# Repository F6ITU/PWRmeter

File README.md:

This millwattmeter project has been driven by 

(c) Dietmar Krause, DL2SBA

License see https://creativecommons.org/licenses/by/4.0/

All software update, construction and calibration hints could be found at 

http://www.dl2sba.com/index.php/elektronik/messtechnik/rf-powermeter

This board  supports two power rails, an Arduino nano and 
3 Molex kk connectors to fit the power input, an Itead Nextion touche display, and
an "all in one" RF detector designed by SV1AFN including : 
An AD8318 det.log, a 12 bits ADC and a low noise 5V power supply. All details at 

https://www.sv1afn.com/ad8318.html

This is a one day project, even for unexperimented ham/hackers. 

Board's dimension is 5x10 cm. 
Two boards could be panelized to fit in a 10x10 standard pcb format
(Itead, Dirt Cheap pcb, Seeed Studio etc)

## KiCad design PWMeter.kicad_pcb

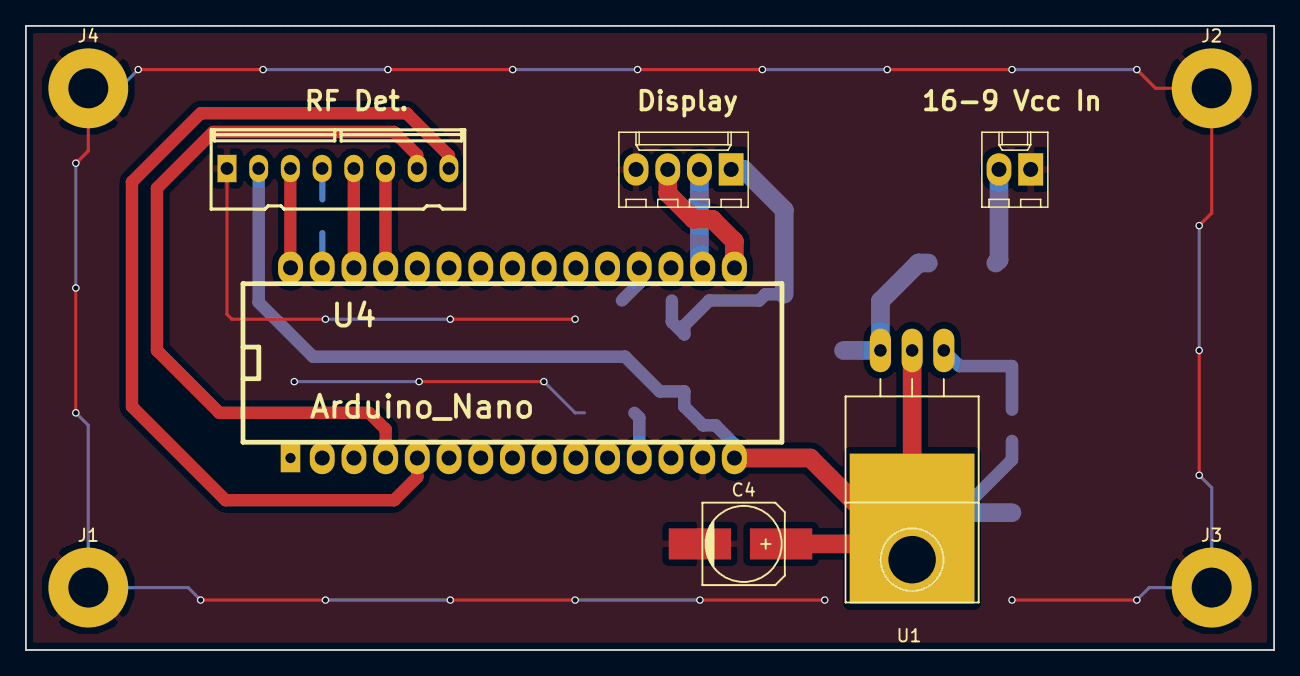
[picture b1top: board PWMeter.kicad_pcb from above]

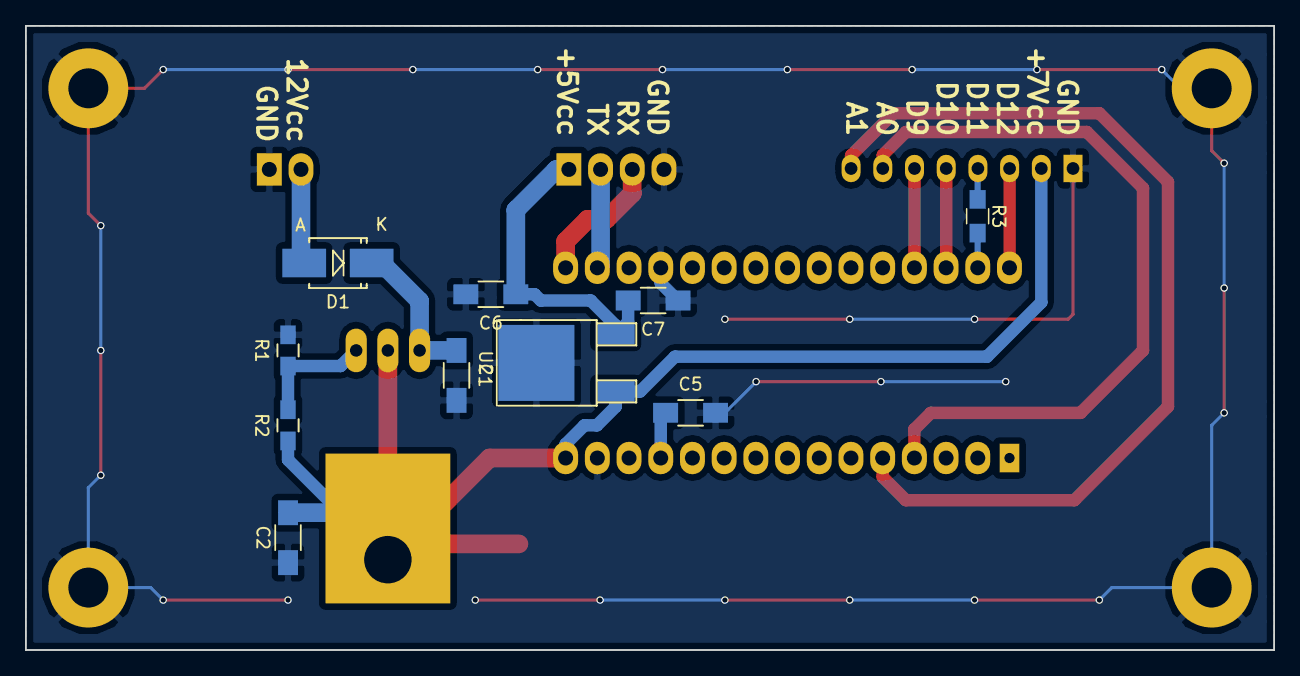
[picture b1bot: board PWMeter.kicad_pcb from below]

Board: 2 copper layers, 100.0 x 50.0 mm, 20 parts (10 on the bottom side), 16 nets.

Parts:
 : 16/9V in; Molex_KK-6410-02_02x2.54mm_Straight
 #2: Display; Molex_KK-6410-04_04x2.54mm_Straight
 #3: kk100_22-23-2081
C1, C2, C5, C6, C7: 100n; C_1206_HandSoldering
C4: 1500uF; c_elec_6.3x7.7
D1: D_Schottky; SMB_Handsoldering
J1, J2, J3, J4: TEST_1P; MountingHole_3.2mm_M3_Pad
R1: 110; C_0805_HandSoldering
R2: 240; C_0805_HandSoldering
R3: R; R_0805_HandSoldering
U1: LM317T; TO-220_Neutral123_Horizontal_LargePads
U2: MC78M05CDT; TO-252-2Lead
U4: Arduino_Nano; arduino_nano

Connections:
+5C: #2.1, C6.1, C7.2, U2.3
+8V: #3.2, C2.1, C4.1, R2.1, U1.2, U2.1, U4.15
+12V: .2, D1.2
GND: .1, #2.4, #3.1, C1.2, C2.2, C4.2, C5.2, C6.2, C7.1, J1.1, J2.1, J3.1, J4.1, R1.2, U2.2, U4.14, U4.19
unnamed: C1.1, D1.1, U1.3
unnamed: C5.1, U4.12
unnamed: #3.3, U4.30
unnamed: #3.4, R3.1
unnamed: #3.5, U4.28
unnamed: #3.6, U4.27
unnamed: #3.7, U4.4
unnamed: #3.8, U4.5
unnamed: #2.2, U4.17
unnamed: #2.3, U4.16
unnamed: R1.1, R2.2, U1.1
unnamed: R3.2, U4.29

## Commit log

2017-07-16 first release
2017-07-16 minor changes on sylkmask
2017-07-16 resistor added on MISO trace
